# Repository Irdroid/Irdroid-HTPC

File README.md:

**Irdroid HTPC Infrared Remote Control Receiver for Kodi and alternatives**
-
**Introduction** 

The Irdroid-HTPC is a USB Infrared Remote Control receiver for HTPC media centers such as  KODI, Plex, Emby, OSMC, Jellyfin, Stremio etc. It enumerates on the host system as a standard HID input device (keyboard) and sends keystrokes to the host system based on the pressed TV remote control key. .(https://irdroid.eu/product/irdroid-htpc-infrared-remote-control-receiver-kodi-alternatives/)

**Product Photo:**
-

.png)

**Features:**
-
- Usb Infrared remote control receiver for your HTPC that supports Kodi, Plex, Emby etc.
- Control your HTPC with your TV remote or any other remote
- No drivers needed, enumerates as a usb keyboard
- Infrared receiver with ultra wide reception angle with great sensitivity
- Kodi addon for activating shortcuts for Favourites and Weather via a single button.
- Velcro dots for fixing the unit in a position

**Supported Operating Systems**
-
- GNU Linux
- Mac OS X
- MS Windows
- Android

In addition to the above the module is open source hardware and software , so if you need to do any changes or fork your own version you are free to do so!
Its shipped with the micronucleus bootloader, compatible with the Arduino IDE and in a manner of minutes you can do whatever changes you need by simply plugging the usb cable of the device to your pc and changing the code as per your needs.
Irdroid-HTPC Remote Receiver has a great range and you don’t have to point your remote control directly toward the device it in order to control your media center.

**You have the following keystrokes available for remotely controlling your media center:**
- UP
- DOWN
- LEFT
- RIGHT
- OK/Enter
- Back
- Navigate to Favourites
- Navigate to Weather
- Play/Pause
 
With the above you get full control of your HTPC media center and if you need additional keystrokes / more control you can reprogram it by using the Arduino IDE.

**Product website and Documentation**
-
- [Irdroid-HTPC product Website](https://irdroid.eu/product/irdroid-htpc-infrared-remote-control-receiver-kodi-alternatives/)
- [Documentation, Schematics, Production files and Software for Brickz can be found in this repository.](https://github.com/Irdroid/Irdroid-HTPC)

**Purchase sample unit**
-
- [Irdroid-HTPC product Website](https://irdroid.eu/product/irdroid-htpc-infrared-remote-control-receiver-kodi-alternatives/)

**You want to help with the development?**
-
- Write us an email to info@irdroid.com

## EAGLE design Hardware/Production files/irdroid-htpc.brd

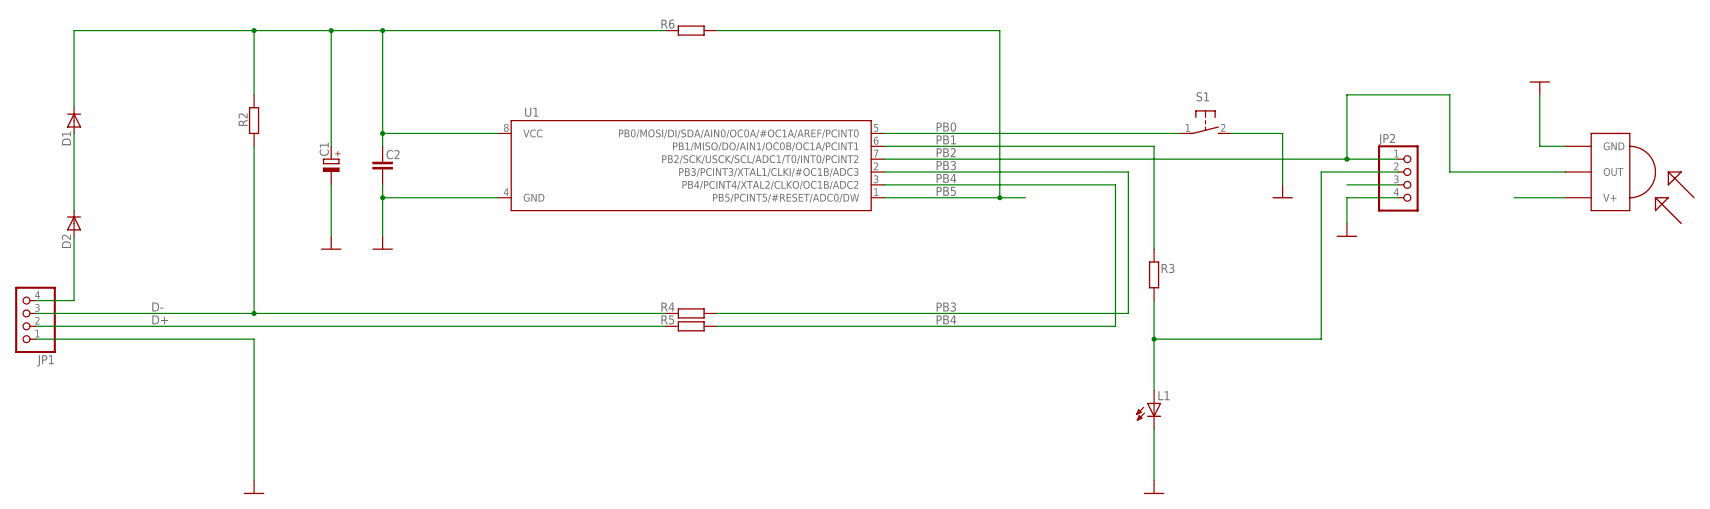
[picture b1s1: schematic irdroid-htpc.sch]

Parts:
C1: CPOL-EUE2-5; E2-5
C2: C-EU025-025X050; C025-025X050
D1, D2: DDO35; DO35-200MILS
JP1, JP2: PINHD-1X4; 1X04
L1: LED3.0MM; LED-3.0MM
R2, R3, R4, R5, R6: R-EU_0204/5; 0204/5
S1: 31-XX; B3F-31XX
U1: ATTINY85-20PU; DIP8
U$1: TSOP1838; TSOP18XX

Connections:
D+: JP1.2, R5.1
D-: JP1.3, R2.1, R4.1
GND: C1.-, C2.2, JP1.1, JP2.4, L1.K (C), S1.2 (S), U1.4 (GND), U$1.GND
unnamed: D1.A, D2.K
unnamed: JP2.2, L1.A, R3.1
PB0: S1.1, U1.5 (PB0/MOSI/DI/SDA/AIN0/OC0A/#OC1A/AREF/PC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)
PB1: R3.2, U1.6 (PB1/MISO/DO/AIN1/OC0B/OC1A/PCINT1)
PB2: JP2.1, U1.7 (PB2/SCK/USCK/SCL/ADC1/T0/INT0/PCINT2), U$1.OUT
PB3: R4.2, U1.2 (PB3/PCINT3/XTAL1/CLKI/#OC1B/ADC3)
PB4: R5.2, U1.3 (PB4/PCINT4/XTAL2/CLKO/OC1B/ADC2)
PB5: R6.2, U1.1 (PB5/PCINT5/#RESET/ADC0/DW)
VBUS: D2.A, JP1.4
VCC: C1.+, C2.1, D1.K, JP2.3, R2.2, R6.1, U1.8 (VCC), U$1.VCC (V+)

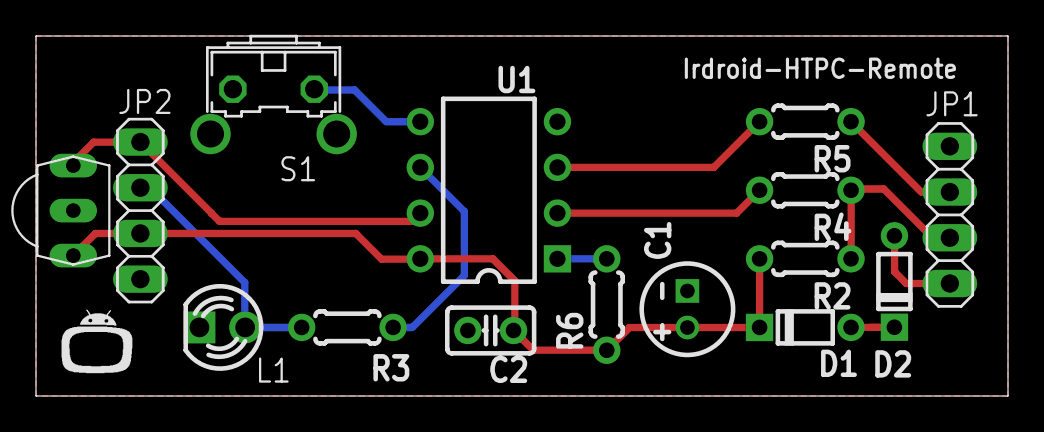
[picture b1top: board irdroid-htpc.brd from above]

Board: 2 copper layers, 54.0 x 20.0 mm, 16 parts (0 on the bottom side), 13 nets.

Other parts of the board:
U$2: IRDROIDLOGO

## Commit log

2021-03-17 Initial release
    Initial release
2021-03-17 Create t85_default.hex.txt
    Added bootloader firmware
2021-03-17 Create tbd.txt
    Added tbd
